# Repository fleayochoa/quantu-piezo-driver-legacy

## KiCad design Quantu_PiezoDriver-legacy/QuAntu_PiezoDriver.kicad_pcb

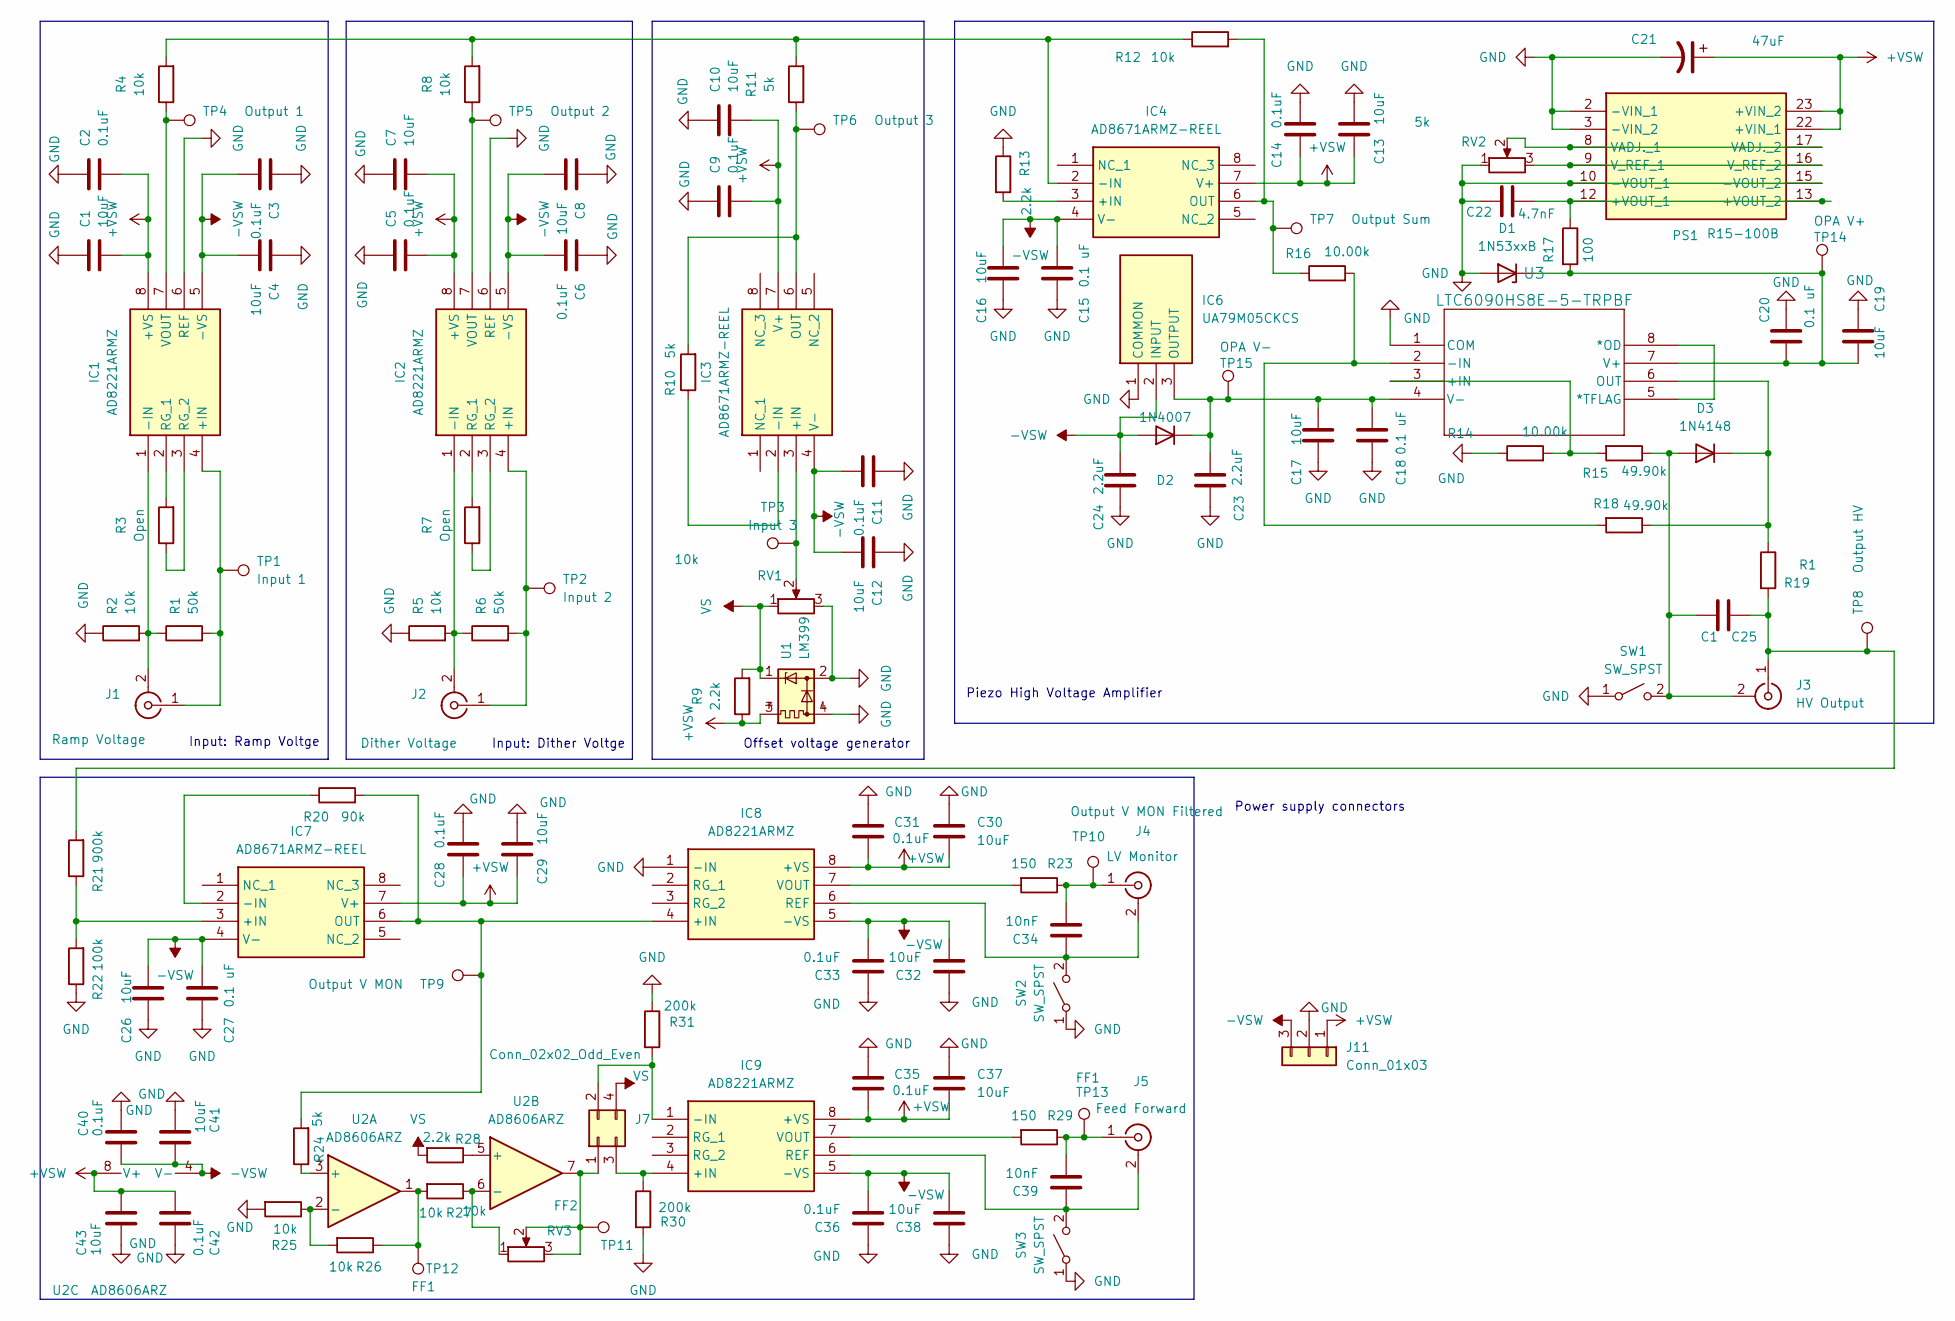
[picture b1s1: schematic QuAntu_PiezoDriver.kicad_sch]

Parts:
C1, C4, C7, C8, C10, C12, C13, C16, C17, C19, C26, C29, C30, C32, C37, C38, C41, C43: 10uF; C_1206_3216Metric_Pad1.33x1.80mm_HandSolder
C2, C3, C5, C6, C9, C11, C14, C28, C31, C33, C35, C36, C40, C42: 0.1uF; C_1206_3216Metric_Pad1.33x1.80mm_HandSolder
C15, C18, C20, C27: 0.1 uF; C_1206_3216Metric_Pad1.33x1.80mm_HandSolder
C21: 47uF; CP_EIA-6032-15_Kemet-U_HandSolder
C22: 4.7nF; C_1206_3216Metric_Pad1.33x1.80mm_HandSolder
C23, C24: 2.2uF; C_1206_3216Metric_Pad1.33x1.80mm_HandSolder
C25: C1; C_1206_3216Metric_Pad1.33x1.80mm_HandSolder
C34, C39: 10nF; C_1206_3216Metric_Pad1.33x1.80mm_HandSolder
D1: 1N53xxB; D_DO-201_P15.24mm_Horizontal
D2: 1N4007; D_DO-41_SOD81_P10.16mm_Horizontal
D3: 1N4148; D_DO-35_SOD27_P7.62mm_Horizontal
IC1, IC2, IC8, IC9: AD8221ARMZ; SOP65P490X110-8N; Mouser Part Number 584-AD8221ARMZ
IC3, IC4, IC7: AD8671ARMZ-REEL; SOP65P490X110-8N; Mouser Part Number 584-AD8671ARMZ-R
IC6: UA79M05CKCS; TO254P470X1016X1965-3P; Mouser Part Number 595-UA79M05CKCS
J1: Ramp Voltage; BNC_Amphenol_B6252HB-NPP3G-50_Horizontal
J2: Dither Voltage; BNC_Amphenol_B6252HB-NPP3G-50_Horizontal
J3: HV Output; SMA_Amphenol_132203-12_Horizontal
J4: LV Monitor; BNC_Amphenol_B6252HB-NPP3G-50_Horizontal
J5: Feed Forward; BNC_Amphenol_B6252HB-NPP3G-50_Horizontal
J7: Conn_02x02_Odd_Even; PinSocket_2x02_P2.54mm_Vertical
J11: Conn_01x03; JST_XH_B3B-XH-A_1x03_P2.50mm_Vertical
PS1: R15-100B; R15100B; Mouser Part Number 919-R15-100B
R1, R6: 50k; R_1206_3216Metric_Pad1.30x1.75mm_HandSolder
R2, R4, R5, R8, R12, R25, R26, R27: 10k; R_1206_3216Metric_Pad1.30x1.75mm_HandSolder
R3, R7: Open; R_1206_3216Metric_Pad1.30x1.75mm_HandSolder
R9, R13, R28: 2.2k; R_1206_3216Metric_Pad1.30x1.75mm_HandSolder
R10, R11, R24: 5k; R_1206_3216Metric_Pad1.30x1.75mm_HandSolder
R14, R16: 10.00k; R_1206_3216Metric_Pad1.30x1.75mm_HandSolder
R15, R18: 49.90k; R_1206_3216Metric_Pad1.30x1.75mm_HandSolder
R17: 100; R_1206_3216Metric_Pad1.30x1.75mm_HandSolder
R19: R1; R_1206_3216Metric_Pad1.30x1.75mm_HandSolder
R20: 90k; R_1206_3216Metric_Pad1.30x1.75mm_HandSolder
R21: 900k; R_1206_3216Metric_Pad1.30x1.75mm_HandSolder
R22: 100k; R_1206_3216Metric_Pad1.30x1.75mm_HandSolder
R23, R29: 150; R_1206_3216Metric_Pad1.30x1.75mm_HandSolder
R30, R31: 200k; R_1206_3216Metric_Pad1.30x1.75mm_HandSolder
RV1, RV3: 10k; Potentiometer_Bourns_3339H_Vertical
RV2: 5k; Potentiometer_Bourns_3339H_Vertical
SW1, SW2, SW3: SW_SPST; PinHeader_1x02_P2.54mm_Vertical
TP1: Input 1; TestPoint_Pad_D2.0mm
TP2: Input 2; TestPoint_Pad_D2.0mm
TP3: Input 3; TestPoint_Pad_D2.0mm
TP4: Output 1; TestPoint_Pad_D2.0mm
TP5: Output 2; TestPoint_Pad_D2.0mm
TP6: Output 3; TestPoint_Pad_D2.0mm
TP7: Output Sum; TestPoint_Pad_D2.0mm
TP8: Output HV; TestPoint_Pad_D2.0mm
TP9: Output V MON; TestPoint_Pad_D2.0mm
TP10: Output V MON Filtered; TestPoint_Pad_D2.0mm
TP11: FF2; TestPoint_Pad_D2.0mm
TP12, TP13: FF1; TestPoint_Pad_D2.0mm
TP14: OPA V+; TestPoint_Pad_D2.0mm
TP15: OPA V-; TestPoint_Pad_D2.0mm
U1: LM399; Analog_TO-46-4_ThermalShield
U2: AD8606ARZ; SOIC-8_3.9x4.9mm_P1.27mm
U3: LTC6090HS8E-5-TRPBF; SO-8_S_LIT

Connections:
+VSW: C1.2, C2.2, C5.2, C7.2, C9.2, C10.2, C13.2, C14.2, C21.1, C28.2, C29.2, C30.2, C31.2, C35.2, C37.2, C42.2, C43.2, IC1.8 (+VS), IC2.8 (+VS), IC3.7 (V+), IC4.7 (V+), IC7.7 (V+), IC8.8 (+VS), IC9.8 (+VS), J11.1, PS1.22 (+VIN_1), PS1.23 (+VIN_2), R9.1, U1.3, U2.8 (V+)
-VSW: C3.2, C4.2, C6.2, C8.2, C11.2, C12.2, C15.2, C16.2, C24.2, C26.2, C27.2, C32.2, C33.2, C36.2, C38.2, C40.2, C41.2, D2.2 (A), IC1.5 (-VS), IC2.5 (-VS), IC3.4 (V-), IC4.4 (V-), IC6.2 (INPUT), IC7.4 (V-), IC8.5 (-VS), IC9.5 (-VS), J11.3, U2.4 (V-)
GND: C1.1, C2.1, C3.1, C4.1, C5.1, C6.1, C7.1, C8.1, C9.1, C10.1, C11.1, C12.1, C13.1, C14.1, C15.1, C16.1, C17.1, C18.1, C19.1, C20.1, C21.2, C22.1, C23.1, C24.1, C26.1, C27.1, C28.1, C29.1, C30.1, C31.1, C32.1, C33.1, C35.1, C36.1, C37.1, C38.1, C40.1, C41.1, C42.1, C43.1, D1.2 (A), IC1.6 (REF), IC2.6 (REF), IC6.1 (COMMON), IC8.1 (-IN), J11.2, PS1.2 (-VIN_1), PS1.3 (-VIN_2), PS1.10 (-VOUT_1), PS1.15 (-VOUT_2), R2.1, R5.1, R13.1, R14.1, R22.1, R25.2, R30.2, R31.1, RV1.3, RV2.1, SW1.1 (A), SW2.1 (A), SW3.1 (A), U1.2, U1.4, U3.1 (COM)
unnamed: C19.2, C20.2, D1.1 (K), R17.2, TP14.1, U3.7 (V+)
unnamed: C17.2, C18.2, C23.2, D2.1 (K), IC6.3 (OUTPUT), TP15.1, U3.4 (V-)
unnamed: C25.2, D3.2 (A), J3.2 (Ext), R15.1, SW1.2 (B)
unnamed: D3.1 (K), R18.1, R19.1, U3.6 (OUT)
unnamed: IC1.4 (+IN), J1.1 (In), R1.2, TP1.1
unnamed: IC1.1 (-IN), J1.2 (Ext), R1.1, R2.2
unnamed: IC1.2 (RG_1), R3.2
unnamed: IC1.3 (RG_2), R3.1
unnamed: IC1.7 (VOUT), R4.1, TP4.1
unnamed: IC2.4 (+IN), J2.1 (In), R6.2, TP2.1
unnamed: IC2.1 (-IN), J2.2 (Ext), R5.2, R6.1
unnamed: IC2.2 (RG_1), R7.2
unnamed: IC2.3 (RG_2), R7.1
unnamed: IC2.7 (VOUT), R8.1, TP5.1
unnamed: IC3.3 (+IN), RV1.2, TP3.1
unnamed: IC3.2 (-IN), R10.1
unnamed: IC3.6 (OUT), R10.2, R11.1, TP6.1
unnamed: IC4.3 (+IN), R13.2
unnamed: IC4.2 (-IN), R4.2, R8.2, R11.2, R12.1
unnamed: IC4.6 (OUT), R12.2, R16.1, TP7.1
unnamed: IC7.3 (+IN), R21.1, R22.2
unnamed: IC7.2 (-IN), R20.1
unnamed: IC7.6 (OUT), IC8.4 (+IN), R20.2, R24.2, TP9.1
unnamed: C34.1, IC8.6 (REF), J4.2 (Ext), SW2.2 (B)
unnamed: IC8.7 (VOUT), R23.2
unnamed: IC9.4 (+IN), J7.3, R30.1
unnamed: IC9.1 (-IN), J7.2, R31.2
unnamed: C39.1, IC9.6 (REF), J5.2 (Ext), SW3.2 (B)
unnamed: IC9.7 (VOUT), R29.2
unnamed: C25.1, J3.1 (In), R19.2, R21.2, TP8.1
unnamed: C34.2, J4.1 (In), R23.1, TP10.1
unnamed: C39.2, J5.1 (In), R29.1, TP13.1
unnamed: J7.1, RV3.2, RV3.3, TP11.1, U2.7
unnamed: C22.2, PS1.12 (+VOUT_1), PS1.13 (+VOUT_2), R17.1
unnamed: PS1.8 (VADJ._1), PS1.17 (VADJ._2), RV2.2
unnamed: PS1.9 (V_REF_1), PS1.16 (V_REF_2), RV2.3
unnamed: R26.1, R27.2, TP12.1, U2.1
unnamed: R24.1, U2.3 (+)
unnamed: R25.1, R26.2, U2.2 (-)
unnamed: R28.1, U2.5 (+)
unnamed: R27.1, RV3.1, U2.6 (-)
unnamed: U3.5 (*TFLAG), U3.8 (*OD)
unnamed: R14.2, R15.2, U3.3 (+IN)
unnamed: R16.2, R18.2, U3.2 (-IN)
VS: J7.4, R9.2, R28.2, RV1.1, U1.1

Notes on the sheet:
Power supply connectors
Piezo High Voltage Amplifier
Input: Ramp Voltge
Offset voltage generator
Input: Dither Voltge

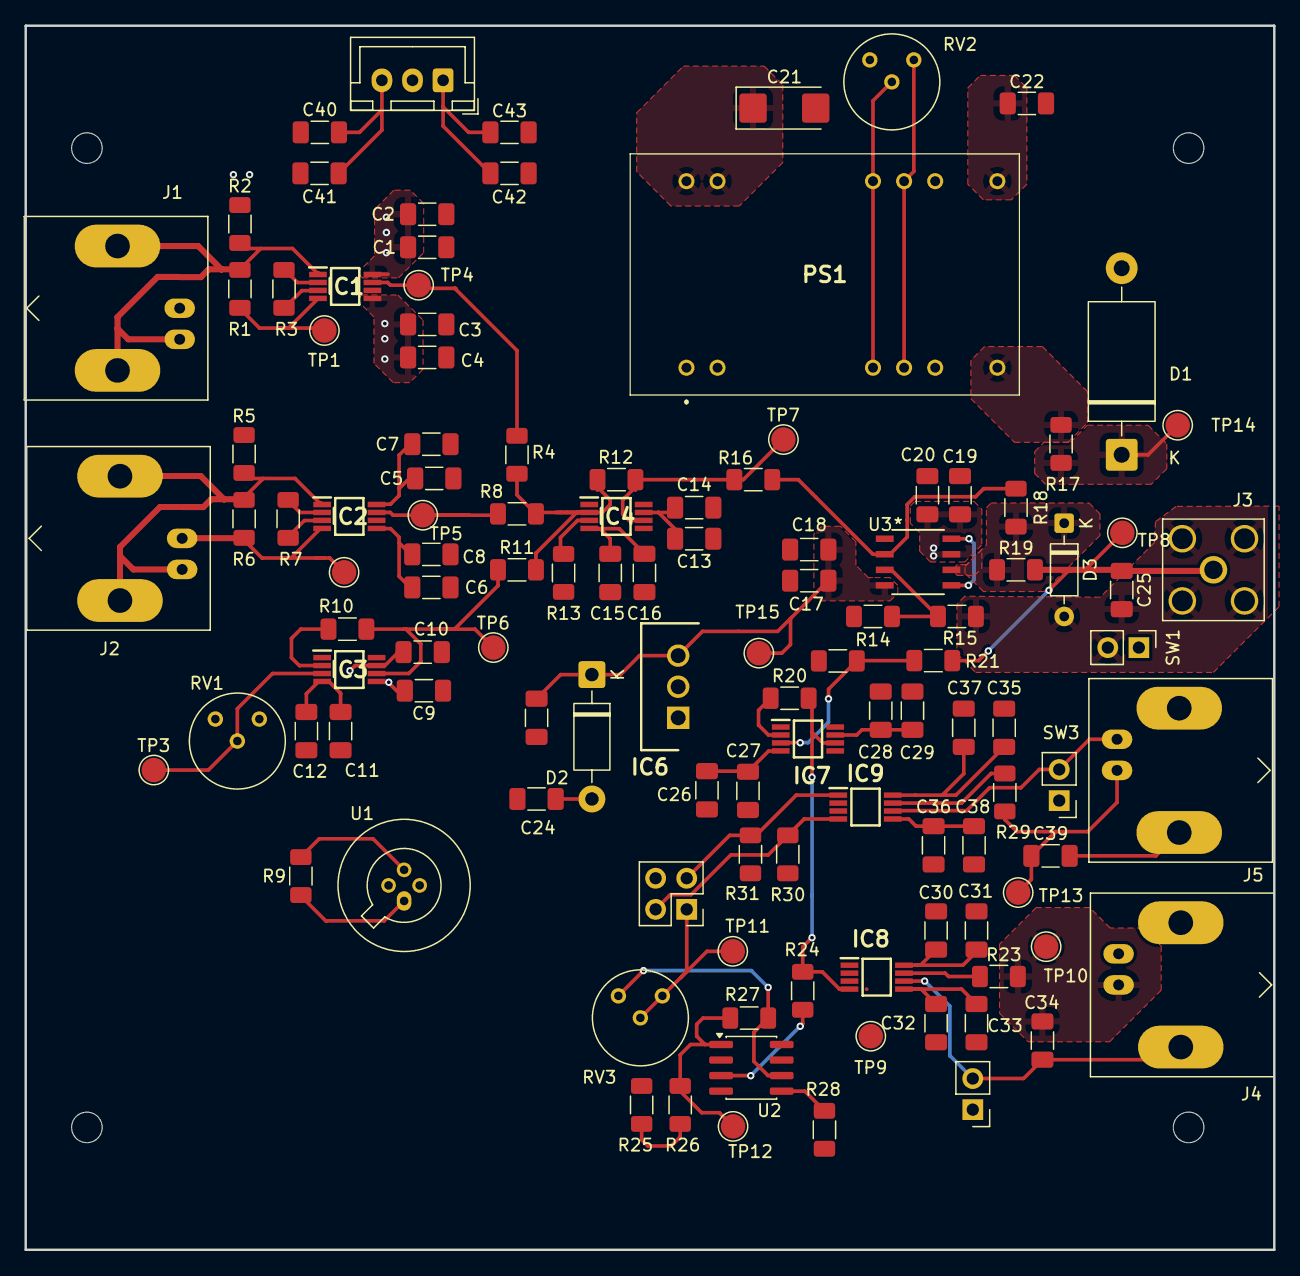
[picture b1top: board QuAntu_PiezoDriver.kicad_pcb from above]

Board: 4 copper layers, 102.0 x 100.0 mm, 121 parts (0 on the bottom side), 48 nets.

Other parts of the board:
Mount1, Mount1#2, Mount1#3, Mount1#4: MH2.5mm; MountingHole_2.5mm
